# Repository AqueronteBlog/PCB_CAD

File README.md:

# PCB_CAD
Examples/Libraries of PCB made for Altium and KidCAD

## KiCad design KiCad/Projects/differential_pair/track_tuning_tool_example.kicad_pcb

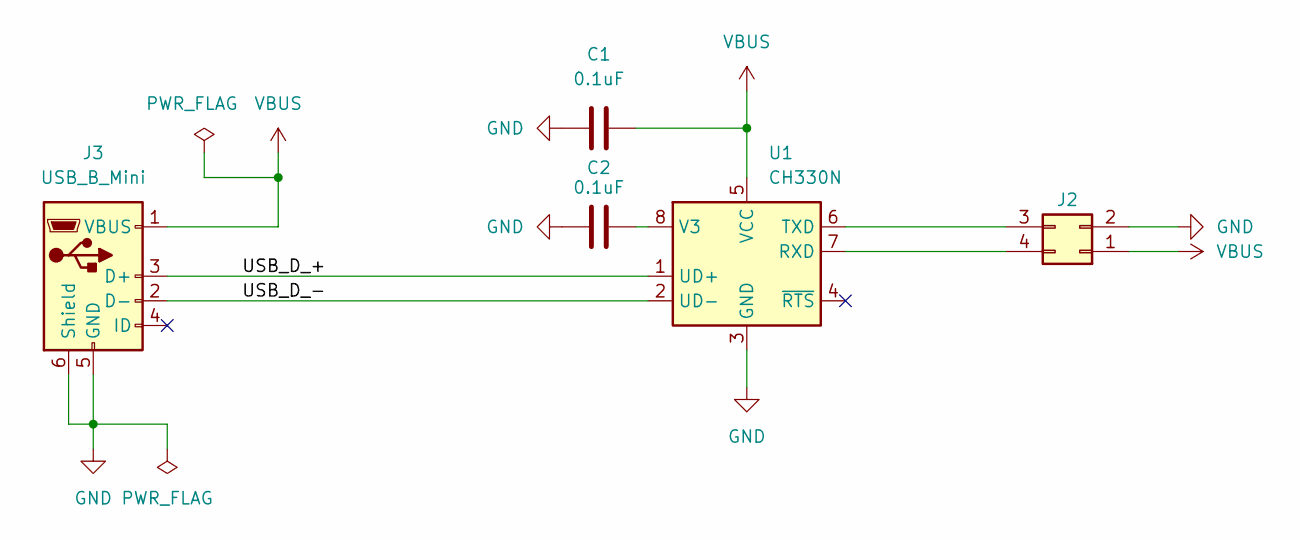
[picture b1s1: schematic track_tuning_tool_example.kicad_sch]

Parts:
C1, C2: 0.1uF; C_0805_2012Metric
J2: Conn_02x02_Counter_Clockwise; PinHeader_2x02_P1.27mm_Vertical_SMD
J3: USB_B_Mini; USB_Mini-B_Lumberg_2486_01_Horizontal
U1: CH330N; SOP-8_3.9x4.9mm_P1.27mm

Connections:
/USB_D_+: J3.3 (D+), U1.1 (UD+)
/USB_D_-: J3.2 (D-), U1.2 (UD-)
GND: C1.1, C2.1, J2.2, J3.5 (GND), J3.6 (Shield), U1.3 (GND)
unnamed: J2.3, U1.6 (TXD)
unnamed: J2.4, U1.7 (RXD)
unnamed: C2.2, U1.8 (V3)
VBUS: C1.2, J2.1, J3.1 (VBUS), U1.5 (VCC)

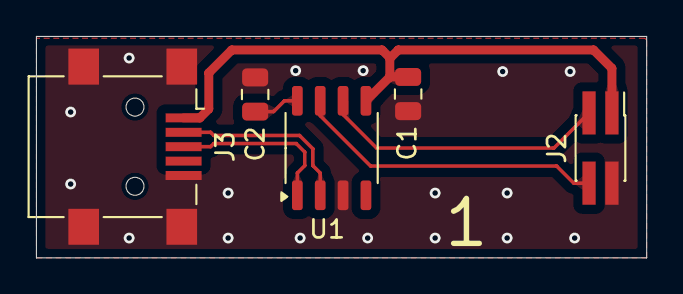
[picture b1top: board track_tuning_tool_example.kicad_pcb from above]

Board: 2 copper layers, 33.9 x 12.3 mm, 5 parts (0 on the bottom side), 7 nets.

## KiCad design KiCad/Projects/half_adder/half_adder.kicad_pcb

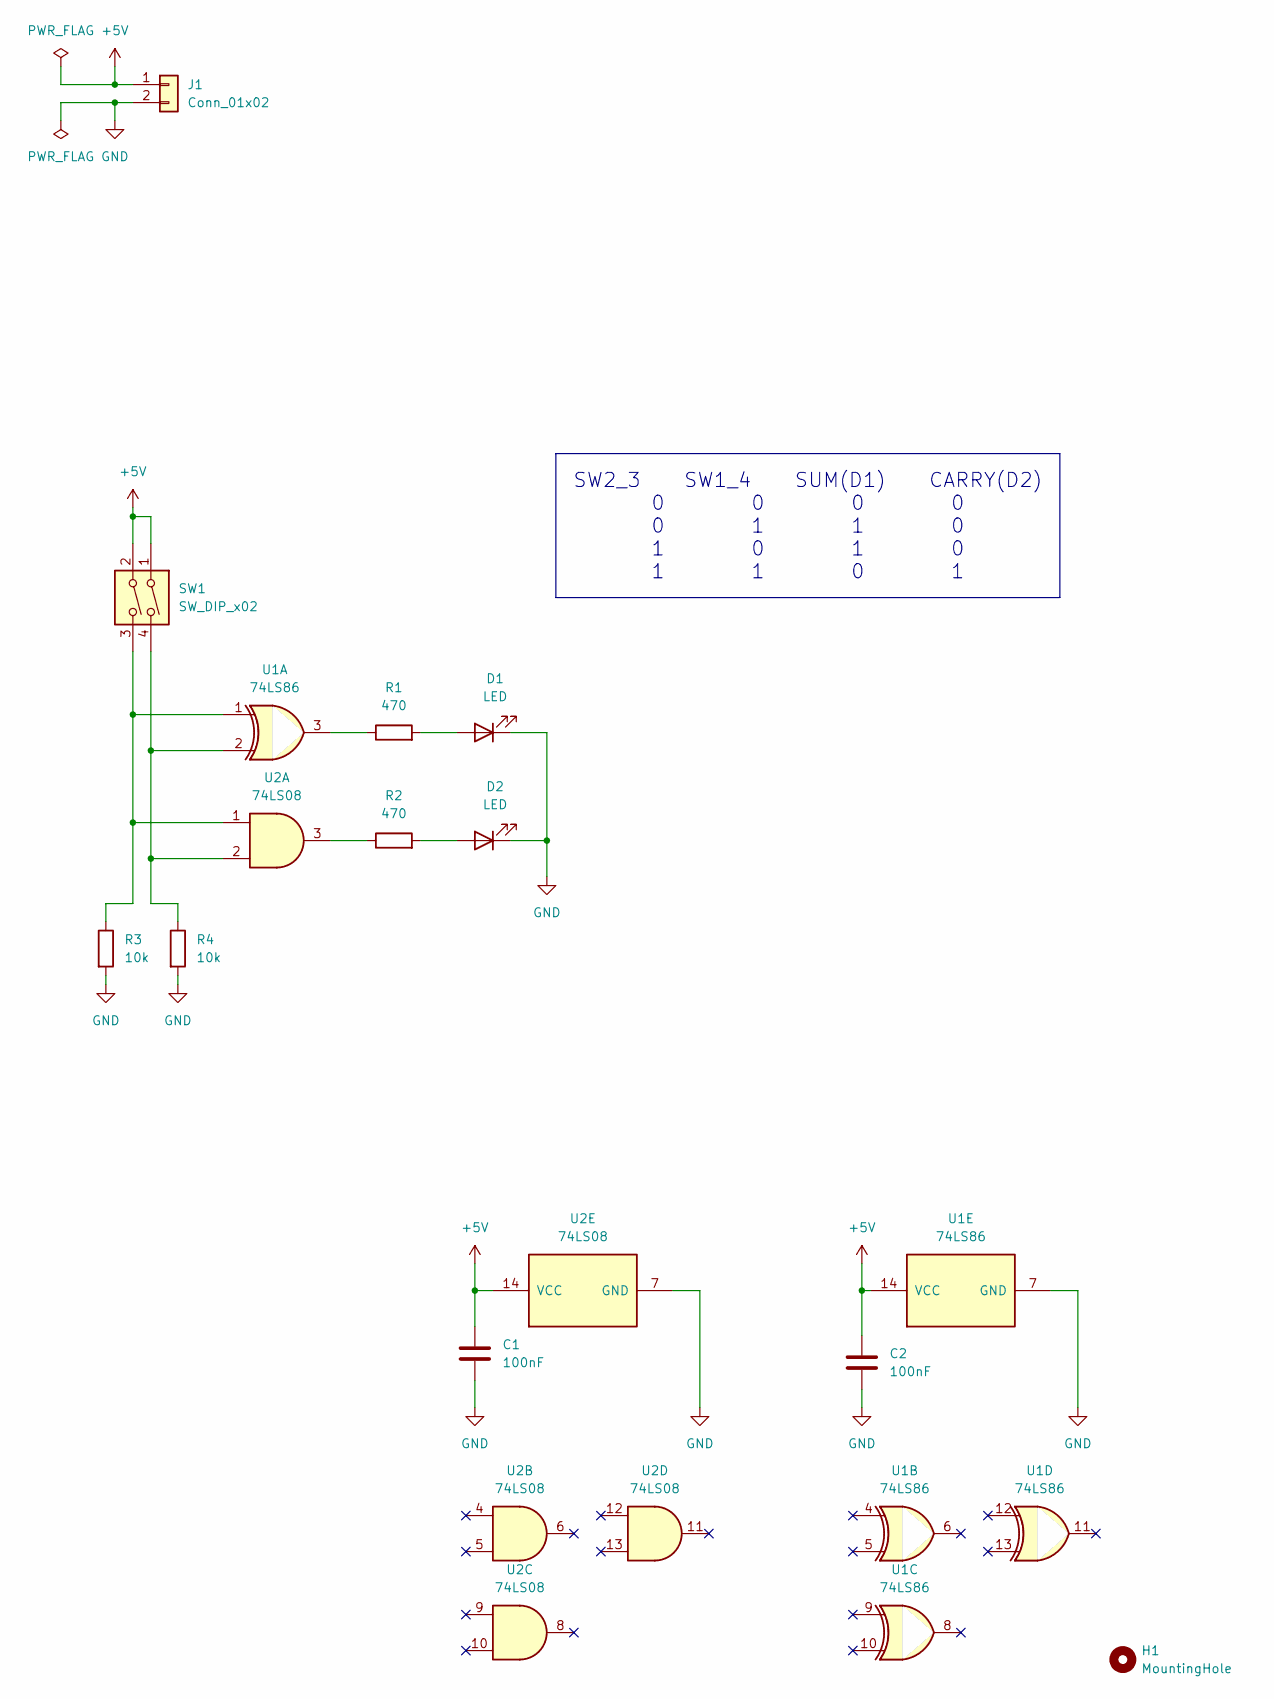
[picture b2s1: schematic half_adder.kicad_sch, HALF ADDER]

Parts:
C1, C2: 100nF; C_0805_2012Metric
D1, D2: LED; LED_0805_2012Metric
H1: MountingHole; MountingHole_3.2mm_M3
J1: Conn_01x02; PinHeader_1x02_P2.54mm_Horizontal
R1, R2: 470; R_0805_2012Metric
R3, R4: 10k; R_0805_2012Metric
SW1: SW_DIP_x02; SW_DIP_SPSTx02_Slide_6.7x6.64mm_W6.73mm_P2.54mm_LowProfile_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
U1: 74LS86; DIP-14_W7.62mm_Socket_LongPads
U2: 74LS08; DIP-14_W7.62mm_Socket_LongPads

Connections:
+5V: C1.1, C2.1, J1.1, SW1.1, SW1.2, U1.14 (VCC), U2.14 (VCC)
GND: C1.2, C2.2, D1.1 (K), D2.1 (K), J1.2, R3.2, R4.2, U1.7 (GND), U2.7 (GND)
unnamed: D1.2 (A), R1.2
unnamed: D2.2 (A), R2.2
unnamed: R1.1, U1.3
unnamed: R2.1, U2.3
unnamed: R3.1, SW1.3, U1.1, U2.1
unnamed: R4.1, SW1.4, U1.2, U2.2

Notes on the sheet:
SW2_3 SW1_4 SUM(D1) CARRY(D2) 0 0 0 0 0 1 1 0 1 0 1 0 1 1 0 1

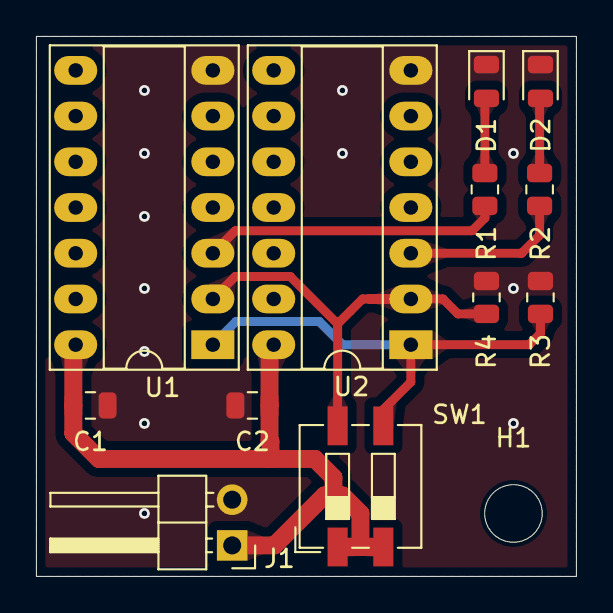
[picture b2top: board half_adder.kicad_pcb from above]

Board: 2 copper layers, 30.0 x 30.0 mm, 13 parts (0 on the bottom side), 8 nets.

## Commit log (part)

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2017-08-31 TEMPLATE. Sheet template A4 according to standards ISO 7200:2004 and ISO 5457:1999 was added.
2017-08-31 LIBRARIES. Bosh Environmental Sensors integrated library created with the BME680 component.
2017-08-31 LIBRARIES. Bosh foot ptints library was created.
2017-09-01 LIBRARIES. Footprint for BME680 is ready into the Bosh FootPrints library.
2017-09-04 LIBRARIES. BME680 3D model added from 3D ContentCentral
2017-09-04 LIBRARIES. BME680 minor changes, last revision: Schematic, Footprint and 3D model.
2017-09-04 LIBRARIES. BME680 3D model updated, the point pointing to pin 1 is on the right place.
2017-09-04 LIBRARIES. 3D Model for BME680 with the point pointing to pin 1 on the right place.
2017-09-05 LIBRARIES. Fixed right name for Bosch sensors.
2017-09-05 LIBRARIES. Measurement Specialties Sensors integrated library created with the HTU21D component.
2017-09-05 LIBRARIES. Measurement Specialties footprint created. HTU21D in progress.
2017-09-06 LIBRARIES. Footprint for HTU21D fixed according to IPC7351C standard
2017-09-06 LIBRARIES. 3D model for HTU21D from 3D Contentcentral
2017-09-13 LIBRARIES. HX711 symbol created.
2017-09-13 LIBRARIES. Avia Semiconductor footprints file created.
2017-09-13 LIBRARIES. Pads created for HX711 device in Avia_Semiconductor_Footprints.
2017-09-13 LIBRARIES. 3D model for HX711 device added ( downloaded from DFRobot ).
2017-09-13 LIBRARIES. HX711 device created in Avia_Semiconductor_Footprints.
2017-09-19 LIBRARIES. Footprints file for Texas Instruments was created
2017-09-19 LIBRARIES. ADS1231 footprint in Texas_Instruments_Footprints was started, component outline is ready
2017-09-19 LIBRARIES. Texas_Intsruments footprints, ADS1231 footprint was included
2017-09-19 LIBRARIES. Texas Instruments for ADC precision was added with the ADS1231 model inside
2017-09-25 LIBRARIES. NXP_DACs_and_ACDs library was created with the PCF8591 symbol included
2017-09-26 LIBRARIES. NXP footprints file was created
2017-09-26 LIBRARIES. PDIP-16 created for PCF8591
2017-09-27 LIBRARIES. PCF8591 PDIP footprint was added.
2017-10-02 LIBRARIES. DIP16 footprint was added for MAX7219
2017-10-02 LIBRARIES. SO16 footprint was started for PCF8591 into NXP_footprints.
2017-10-03 LIBRARIES. 3D model for PCF8591 was added
2017-10-03 LIBRARIES. The device PCF8591 was completed with all its footprints.
2017-10-06 LIBRARIES. MAX7219/72221 symbol was created inside the MAXIM_Display_Power_and_Control library.
2017-10-09 LIBRARIES. MAXIM footprints file was created. MAX7219/7222 component outline was created
2017-10-09 LIBRARIES. SOIC-24 was created for MAX7219/7221
2017-10-10 LIBRARIES. 3D Model for MAX7219/7221 device
2017-10-10 LIBRARIES. PDIP24 was created for MAX7219/7221
2017-10-10 LIBRARIES. MAX7219/7221 PDIP footprint added for this device.
2017-10-17 LIBRARIES. Footprints file with HMC5883L sensor added
2017-10-17 LIBRARIES. Honeywell library was created with the HMC5883L sensor included
2017-10-17 LIBRARIES. Honeywell 3D model for HMC5883L sensor included
2017-10-18 LIBRARIES. NXP I2C General Purpose IO was created with the symbols: PCF8574 ( 16 pins and 20 pins )
2017-10-18 LIBRARIES. 3D model for SOP 20pins was added.
2017-10-20 LIBRARIES. Silabs footprint file was created for Altium
2017-10-20 LIBRARIES. Silabs sensor file was created for Altium with SI7006 symbol included
2017-10-23 LIBRARY. NXP I2C led controllers was just created with the PCA9685 symbol device inside ( both symbols: HVQFN28 and TSSOP28 )
2017-10-24 LIBRARIES. Working on a new footprint for NXP footprints file.
2017-10-24 LIBRARIES. New 3D step model added for SOP28 into NXP folder
2017-10-24 LIBRARIES. NXP footprint. TSSOP-28 was added to the library.
2017-10-31 LIBRARIES. NXP footprint, component outline for HVQFN28 is done.
2017-10-31 LIBRARIES. NXP footprint, HVQFN28 is done and ready to be used.
2017-10-31 LIBRARIES. PCA9685 symbol is ready to be used.
2017-11-08 LIBRARIES. Nordic footprints file was just created.
2017-11-13 LIBRARIES. NRF51422 QFN48 symbol with its footprint was added into Nordic Microcontroller file for Altium
2017-11-13 LIBRARIES. NRF51422 QFN48 footprint was added into Nordic footprints
2017-11-13 LIBRARIES. Basic 3D model for NRF51422-QNF48 was added.
2017-11-20 LIBRARIES. NRF51422 footprint CDAB WLCSP was created
2017-11-21 LIBRARIES. Nordic Semiconductor CFAC WLCSP package footprint added.
2017-11-22 LIBRARIES. Panasonic footprints file was created
2017-11-22 LIBRARIES. Panasonic sensors library was created with AN48836B symbol.
2017-11-22 LIBRARIES. Simple Panasonic 3D model for AN48836B device was added.
2017-11-23 LIBRARIES. STMelectronics footprint file was created
2017-11-23 LIBRARIES. LSM303AH footprint was created into STMelectronics footprint
2017-11-24 LIBRARIES. Murata footprints file was created for Altium
2017-11-24 LIBRARIES. Murata LoRa module footprint added into Murata footprints file. 3D model needs to be placed.
2017-11-27 LIBRARIES. Murata LoRa module footprint added into Murata footprints file.
2017-11-27 LIBRARIES. 3D model for Murata LoRa module was added ( it was imported from 3D ContentCentral )
2017-11-28 LIBRARIES. Altium. Working on a new footprint for MAXIM_Footprints. DS3231 footprint
2017-11-28 LIBRARIES. Altium. Working on a new footprint for MAXIM_Footprints. DS3231 component outline is ready
2017-11-29 LIBRARIES. Altium. New footprint for MAXIM_Footprints. DS3231 component is ready
2017-11-29 LIBRARIES. Altium. New device: DS3231 into MAXIM_Real_Time_Clocks file.
2017-12-14 LIBRARIES. Semtech footprints file was just created.
2017-12-14 LIBRARIES. Semtech footprints was updated to work with milimeters and the grid was changed..
2017-12-15 LIBRARIES. Footprint for SX1272/73 device was added into SEMTECH Footprint file
2017-12-18 LIBRARIES. A basic 3D model for SX1272/73
2018-01-29 LIBRARIES. Footprint for DS1624 device was just started into MAXIM Footprint file
2018-01-31 LIBRARIES. Basic 3D model for DS1624 was added
2018-01-31 LIBRARIES. Symbol with footprint for DS1624 was added into MAXIM Sensor and Sensor Interface
2018-01-31 LIBRARIES. PDIP8 Footprint for DS1624 device was just started into MAXIM Footprint file
2018-01-31 LIBRARIES. Basic PDIP8 3D model for DS1624 was added
2018-01-31 LIBRARIES. Symbol with PDIP8 footprint for DS1624 was added into MAXIM Sensor and Sensor Interface
2018-02-07 LIBRARIES. Silabs sensor file was created for Altium with SI7021 symbol included
2018-03-14 LIBRARIES. Footprint for AMS was created
2018-03-14 LIBRARIES. AS3933 device was created ( TSSOP and QNF symbol ) inside AMS Wireless Sensor Connectivity library
2018-03-14 LIBRARIES. Basic 3D model for AS3933 device ( TSSOP ) was added
2018-03-15 LIBRARIES. Basic 3D model for AS3933 device ( QFN ) was added
2018-03-15 LIBRARIES. AS3933 device was updated ( QNF symbol, exposed pad was added ) inside AMS Wireless Sensor Connectivity library
2018-03-15 LIBRARIES. AS3933 foorprint ( QFN ) was completed inside AMS footprint
2018-03-20 LIBRARIES. MCP1640 footprint was added into MICROCHIP footprint file.
2018-03-20 LIBRARIES. MCP1640 symbol ( SOT23 and DFN ) were comp-leted, DFN footprint is still under development.
2018-03-20 LIBRARIES. Basic 3D model added for MCP1640_SOT23
2018-03-21 LIBRARIES. MCP1640 symbol and footprint was updated for Microchip.
2018-03-21 LIBRARIES. MCP1640 ( DNF ) footprint was added into MICROCHIP footprint file.
2018-05-03 LIBRARIES. mCube footprint file was created.
2018-05-03 LIBRARIES. MC3635 device was added into mCube footprint file.
2018-05-31 LIBRARIES. iAQ-Core footprint is in progress into AMS footprint file. Pads and Component outline are ready
2018-06-01 LIBRARIES. iAQ-Core footprint is completed and added into AMS footprint file.
2018-06-01 LIBRARIES. iAQ-Core symbol was added into AMD Air Quality Sensors.
2018-06-14 LIBRARIES. Simple 3D model was added for TMP102 device( generated by PCB Library Expert )
2018-07-03 LIBRARIES. TI footprint, TMP102 footprint was added.
2018-07-03 LIBRARIES. TMP102 does NOT belong to MICROCHIP
2018-07-17 LIBRARIES. Maxim footprint, new footprint is in progress for the MAX30100 device.
2018-07-20 LIBRARIES. MAX30100 new component was added.
2018-08-27 Libraries. Simple 3D model for the DS1307 device ( SOIC8 )
2018-08-27 Libraries. Maxim footprints library was updated with a new footprint, SOIC8
2018-08-27 Libraries. Maxim RTC, DS1307 was added.
2018-08-28 LIBRARIES. Microchip footprints was updated with a new footprint for SOIC8
2018-08-28 LIBRARIES. Microchip, new digital potentiometer was added MCP41XXX.
2018-08-29 LIBRARIES. Microchip, PDIP8 is in progress, pads and outline were added
2018-08-29 LIBRARIES. Microchip, new PDIP8 footprint was added
2018-08-29 LIBRARIES. Microchip, MCP41XXX was added the PDIP8 footprint.
2018-08-30 LIBRARIES. Microchip, Basic 3D model PDIP14 was added ( created by PCB library ).
2018-08-30 LIBRARIES. Microchip, MCP41XXX was added the PDIP14 footprint.
2018-08-31 LIBRARIES. Basic 3D model was added for SOIC14 and SOP14 ( PCBLibrary )
2018-09-03 LIBRARIES. Microchip, MCP42XXX and MCP41XXX parts were added
2018-09-05 LIBRARIES. Sensirion footprint file was just created
2018-09-05 LIBRARIES. Basic 3D model for SHT21 ( imported from 3D ContentCentral ) was removed because of bad design
2018-09-05 LIBRARIES. Sensirion SHT2X footprint was added
2018-09-05 LIBRARIES. Environmental sensors library was created with three devices: SHT20, SHT21 and SHT25.
2018-09-17 LIBRARIES. Basic 3D model for BMP180 device was added ( imported from 3D ContentCentral )
2018-09-21 LIBRARIES. Library for BMP180 device was added
2018-10-01 LIBRARIES. Basic 3D model for MAX44009 device was added ( imported from 3D ContentCentral )
2018-10-01 LIBRARIES. New footprint for MAX44009 device was added into MAXIM library
2018-12-12 LIBRARIES. TMP006 footprint has been started, component outline is completed
2018-12-12 LIBRARIES. Basic 3D model was added for TMP006 ( modification of PCBLibrary )
2018-12-12 LIBRARIES. TI Temperature sensor library updated with TMP006 device
2018-12-12 LIBRARIES. TI footprint library updated with TMP006 footprint
2019-01-25 LIBRARIES. Basic 3D model for the PCF85063 device (from PCB Library Expert)
2019-01-25 LIBRARIES. NXP footprint. Footprint for PCF85063 was completed
2019-01-25 LIBRARIES. NXP, new library for Real tiny clock/caldendar. PCF85063 was added
2019-01-28 LIBRARIES. A 3D model for this device (from snapEDA)
2019-01-28 LIBRARIES. New footprint for the AMG8833 device was added to panasonic footprints library
2019-05-28 LIBRARIES. A new basic model for MCP9808 (DFN) from 3D ContentCentral
2019-05-28 Ignore file was updated, do NOT track zip files
2019-05-30 Libraries. Microchip Thermal Sensor library, MCP9808 device was added, library was generated as well
2019-06-04 Libraries. A basic 3D model for the MCP9808 device was added
2019-06-04 Libraries. Microchip footprint was added with a new footprint for MCP9808
2019-06-04 Libraries. Microchip Thermal Sensor library, MCP9808 device was completed
2019-06-12 LIBRARIES. A basic 3D model was added (third party)
2019-06-12 LIBRARIES. HTS221 device was added
2019-06-12 LIBRARIES. A new footprint was added into STM footprints for HTS221 device
2019-06-19 LIBRARIES. New footprint added into STMicroelectronics footprint for LPS22HB device
2019-06-19 LIBRARIES. New component added into STMicroelectronics MEMS library: LPS22HB device
2019-06-20 LIBRARIES. New component added into STMicroelectronics MEMS library: LPS25HB device
2019-06-24 LIBRARIES. New device was added: SX128X.
2019-06-24 LIBRARIES. New footprint was added for SX128x into Semtech foorptints library.
2019-06-24 Ignore file was updated, do NOT track intermidiate files.
2019-08-27 LIBRARIES. A basic 3D model was added for LIS2DTW12 device (this 3D model was imported)
2022-10-19 Template A4 ISO5757 for KiCad
2024-03-16 Kicad. Half-adder project was completed
2024-03-16 Ignore file was updated, do NOT track generated files
2024-07-05 KiCad DB Library. New updates
    New symbols, footprints and 3D models were added for the db KiCad library
2025-10-19 KiCad. Differential pair project
    This project was completed. Neither production files nor manufacturing files were generated.
